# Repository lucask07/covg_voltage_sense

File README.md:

# COVG Voltage Sense Board

This board is physically small so it can be housed in an enclosure on a micromanipulator. The board input is a BNC connector which is compatible with glass microelectrode holders. 

The input amplifier must have low capacitance to minimize the total filter from the capacitance and the microelectrode resistance. The first version has a fixed amplifier gain. 

The **Rev_b board** modifications were designed and implemented by undergraduate student Jordan Haag. The board incorporates programmable gain and uses a low-noise voltage reference, REF3440, as the reference input to the offset adjust DAC. The low-noise reference improves the noise performance of the system. 

## Schematic
The [schematic](docs/voltage_sense.pdf) is in the DOCS folder.

## Fabrication
The second revision of this board was fabricated and assembled by JLCPCB. 

Order #: Y13-3276043A 

Assembly: SMT02402281623205-3276043A

Date: 2024/02/29

## Bill of Materials

The BOM is here  

Certain parts are not directly available from LCSC and so were pre-ordered. Pre-order: 24AA025UID, OPA1641,
DAC101C081CIMK/NOPB, TMUX6111PWR, TCA9555DBR, LP2981A-33DBVT, ADA4000-2ARZ-R7. Global sourcing: 3269W-1-103GLF, REF3440TIDBVR.

## Bugs and Future Improvement

* A footprint for a capacitor should be included in parallel with the feedback gain resistors, for example R33, R34, R35, and R36. This limits the amplifier bandwidth. Currently we work around this omission by stacking a capacitor on top of the resistor. Issue ([#4][i4])

[i4]: https://github.com/lucask07/covg_voltage_sense/issues/4

* U8,U10 (TMUX6111) and U11 (REF3440) were not assembled by JLCPCB and were lated added by hand.

## Upgrades 

This version addresses the following issues that occured with V1 

* DAC reference noise: https://github.com/lucask07/covg_voltage_sense/issues/5
* Negative capacitance connection: https://github.com/lucask07/covg_voltage_sense/issues/3
* C8 causes oscillation: https://github.com/lucask07/covg_voltage_sense/issues/2
* Incorrect BOM resistor values: https://github.com/lucask07/covg_voltage_sense/issues/1

## Miscellaneous

### HDMI: connection from DAQ to daughtercard 

The digital COVG project uses the concept of one main data acquisition board connected to an FPGA. The main data acquisition board has multiple channels that extend to daughtercards. The connection to each daughtercard allows for low-latency control by connections to high-speed ADCs and DACs on the daq board. For COVG the daughtercards are the bath clamp; the guard clamp; the voltage clamp and I force; and the V1/V2. The connectivity to the daughtercard is generalized and will be the same for each. 

An HDMI-A cable is used for input and output signals that connect the bath clamp daughtercard to the DAQ board. The HDMI cable carries:

- **power**: +5V, +15V, -15V
- **GND** 
- **Analog outputs** (to ADCs): 
	- OUT\_P, OUT\_N differential pair (x1) to 5 MSPS ADC 
	- single-ended out AMP\_OUT, CAL\_ADC both to individual channel of 1 MSPS ADC (ADS8686) 
- **Analog reference**: VCM: buffered ADC common-mode voltage (nominal 2.5 V)
- **Digital inputs** (from DACs): 
	- CMD: (command signal) from 1 us settling time DAC (attenuated by x10 at board)
	- CC: (capacitive compensation) from 1 us settling time DAC. AC coupled. 
	- CAL_DAC: from 5 us settling time DAC (DAC8050). Either voltage source or current source (Howland current pump), programmable on DAQ board
- **Digital control** (I2C): SDA, SCL (@ 3.3 V levels). Pull-ups are on DAQ board not on the daughtercards! The daughtercards use a TCA9555 I/O expander to generate many control signals from the I2C interface. 
- **Utiility** grab-bag connected to test-point. Jumper on DAQ board to set to analog in, analog out or digital I/O.

| Pin | HDMI name    | Generic Daughtercard     | Bath clamp | Notes  |
|-----|--------------|--------------|------------|---------------------------------------------------------------------------|
| 1   | Data2+       | fastDAC1     | CMD        | ~1 us settling time                      |
| 2   | Data2 shield | Gnd          | Gnd        |                                                                           |
| 3   | Data2-       | Analog/GPIO1 | CAL_DAC    | Analog input signal from DAC8050, 16 bit, 5us settle, 5 V supply                                                                         |
| 4   | Data1+       | fastADC+     | IM_P       | to AD7960/AD7961. Differential low-pass filter on DAQ board                                                                          |
| 5   | Data1 shield | Gnd          | Gnd        |                                                                           |
| 6   | Data1-       | fastADC-     | IM_N       | to AD7960/AD7961. Differential low-pass filter on DAQ board                                                                          |
| 7   | Data0+       | fastDAC2     | CC         | ~1 us settling time                                                                          |
| 8   | Data0 shield | Gnd          | Gnd        |                                                                           |
| 9   | Data0-       | Analog/GPIO2 | CAL_ADC    | to ADS8686 1 MSPS, programmable PGA for range up to +/-10V                                                           |
| 10  | Clock+       | 15V          | 15V        | From a linear regulator on the DAQ board, 75 mA max per channel                                                                         |
| 11  | Clock shield | Gnd          | Gnd        |                                                                           |
| 12  | Clock-       | VCM          | VCM        | buffered on DAQ board, nominal 2.5 V                                                                          |
| 13  | CEC          | -15V         | -15V       | From a linear regulator on the DAQ board, 75 mA max per channel                             |
| 14  | Reserved     | open         | open       | Resistor jumper on DAQ board sets as analog in, analog out, or digital I/O (@ 3.3 V levels). Default stuffing option is to connect to the general purpose ADC (ADS8686). |
| 15  | SCL          | SCL          | SCL        | I2C clock. Pull-up on main DAQ board, 3.3 V levels                |
| 16  | SDA          | SDA          | SDA        | I2C data. Pull-up on main DAQ board, 3.3 V levels                 |
| 17  | Gnd          | Gnd          | Gnd        |                                                                           |
| 18  | 5V           | 5V           | 5V         | Power input from linear regulator, 200 mA max per channel (target)  |
| 19  | HPD          | Analog/GPIO3 | AMP_OUT    | output to ADS8686 1 MSPS, programmable PGA                        |

### Acknowledgments

Research reported in this repository was supported by the National Institute Of Neurological Disorders And Stroke of the National Institutes of Health under Award Number R15NS116907. The content is solely the responsibility of the authors and does not necessarily represent the official views of the National Institutes of Health.

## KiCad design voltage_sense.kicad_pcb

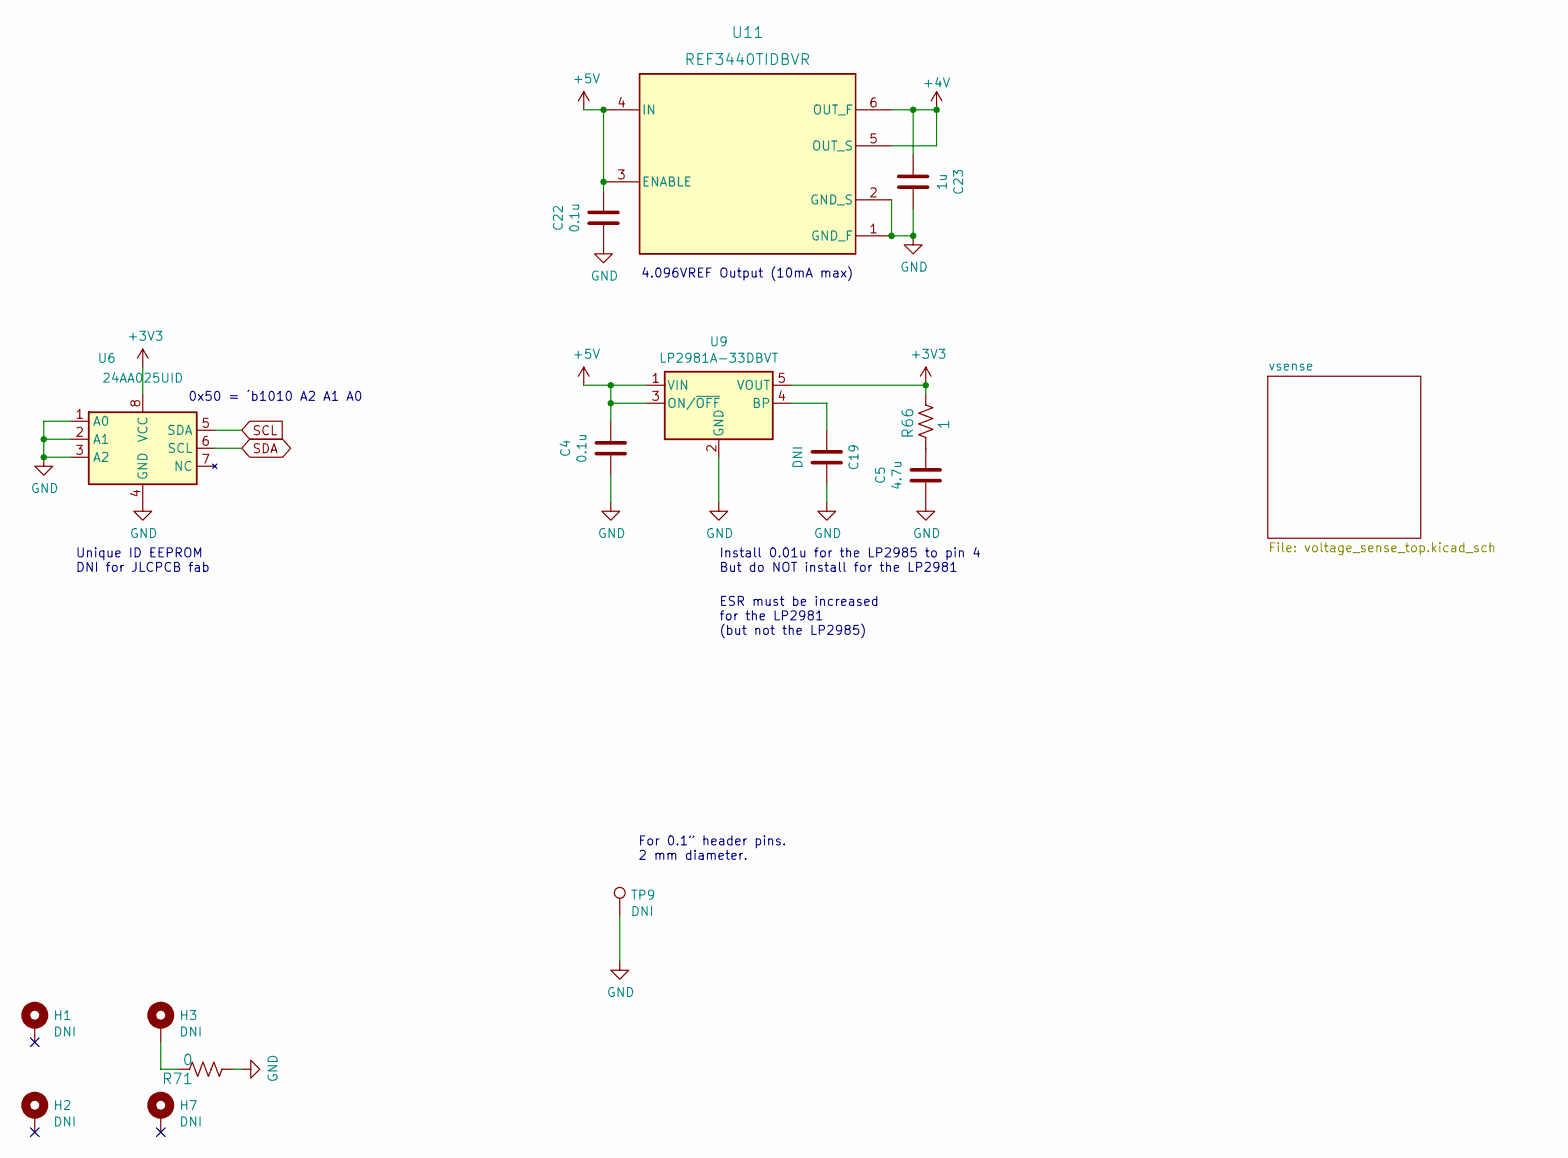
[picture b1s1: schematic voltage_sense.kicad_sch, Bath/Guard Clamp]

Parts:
C4, C22: 0.1u; C_0603_1608Metric; Tolerance 10%; voltage 25V
C5: 4.7u; C_0603_1608Metric; Tolerance 20%; voltage 25V
C19: DNI; C_0603_1608Metric
C23: 1u; C_0603_1608Metric; Tolerance 20%; voltage 25V
H1, H2, H7: DNI; MountingHole_2.2mm_M2
H3: DNI; MountingHole_2.2mm_M2_Pad
R66: 1; R_0603_1608Metric; Tolerance 1%
R71: 0; R_0603_1608Metric; Tolerance 1%
TP9: DNI; TestPoint_THTPad_D2.0mm_Drill1.0mm
U6: 24AA025UID; SOIC-8_3.9x4.9mm_P1.27mm
U9: LP2981A-33DBVT; SOT-23-5
U11: REF3440TIDBVR; REF3440

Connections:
+3V3: R66.1, U6.8 (VCC), U9.5 (VOUT); also elsewhere on the board
+4V: C23.2, U11.5 (OUT_S), U11.6 (OUT_F); also elsewhere on the board
+5V: C4.1, C22.1, U9.1 (VIN), U9.3 (ON/~OFF), U11.3 (ENABLE), U11.4 (IN); also elsewhere on the board
GND: C4.2, C5.2, C19.2, C22.2, C23.1, R71.2, TP9.1, U6.1 (A0), U6.2 (A1), U6.3 (A2), U6.4 (GND), U9.2 (GND), U11.1 (GND_F), U11.2 (GND_S); also elsewhere on the board
unnamed: C5.1, R66.2
unnamed: C19.1, U9.4 (BP)
unnamed: H3.1, R71.1
SCL: U6.5 (SDA); also elsewhere on the board
SDA: U6.6 (SCL); also elsewhere on the board

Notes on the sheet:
For 0.1” header pins. 2 mm diameter.
Install 0.01u for the LP2985 to pin 4 But do NOT install for the LP2981
Unique ID EEPROM DNI for JLCPCB fab
0x50 = ‘b1010 A2 A1 A0
4.096VREF Output (10mA max)
ESR must be increased for the LP2981 (but not the LP2985)

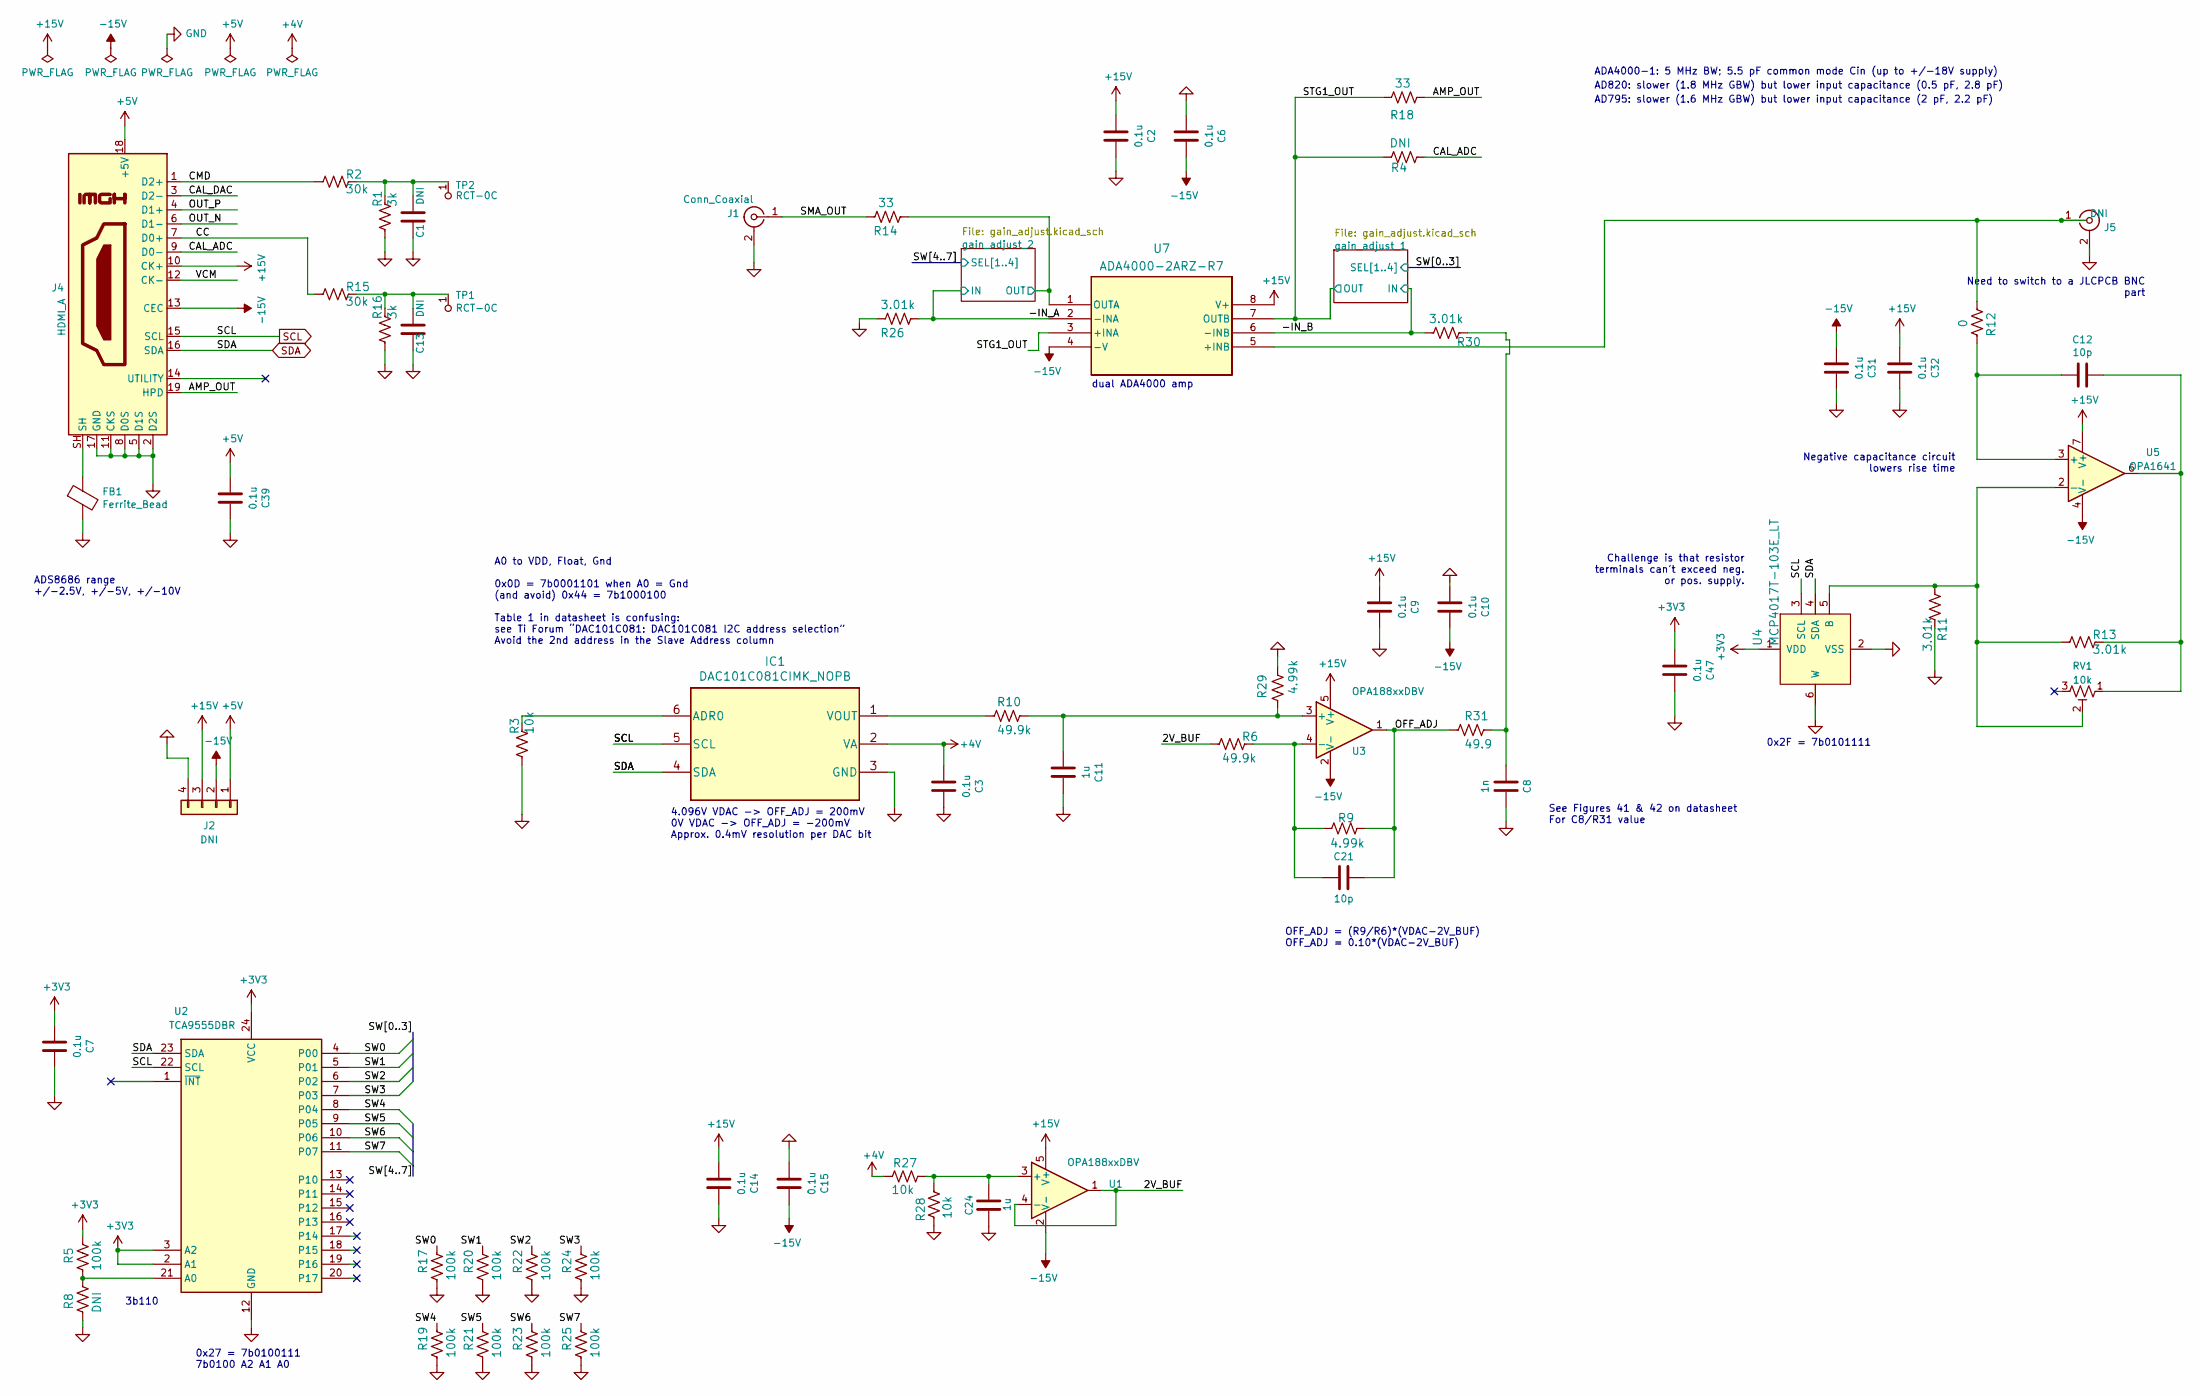
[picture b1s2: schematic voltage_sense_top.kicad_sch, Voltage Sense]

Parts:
C1, C13: DNI; C_0603_1608Metric; Tolerance 5%; voltage 50V
C2, C3, C6, C9, C10, C14, C15, C31, C39: 0.1u; C_0603_1608Metric; Tolerance 20%; voltage 25V
C7, C32, C47: 0.1u; C_0603_1608Metric; voltage 25V
C8: 1n; C_0603_1608Metric; Tolerance 20%; voltage 25V
C11, C24: 1u; C_0603_1608Metric; Tolerance 20%; voltage 25V
C12: 10p; C_0603_1608Metric; Tolerance 5%
C21: 10p; C_0603_1608Metric; Tolerance 20%; voltage 25V
FB1: Ferrite_Bead; C_1206_3216Metric
IC1: DAC101C081CIMK_NOPB; TSOT-23-6
J1: Conn_Coaxial; BU-SMA-G
J2: DNI; PinHeader_1x04_P2.54mm_Horizontal
J4: HDMI_A; CONN_10029449-111RLF_HDMI_A
J5: DNI; BNC_Amphenol_B6252HB-NPP3G-50_Horizontal
R1, R16: 3k; R_0603_1608Metric; Tolerance 1%
R2, R15: 30k; R_0603_1608Metric; Tolerance 1%
R3: 10k; R_0603_1608Metric; Tolerance 5%
R4, R8: DNI; R_0603_1608Metric; Tolerance 1%
R5, R17, R19, R20, R21, R22, R23, R24, R25: 100k; R_0603_1608Metric; Tolerance 1%
R6, R10: 49.9k; R_0603_1608Metric; Tolerance 1%
R9, R29: 4.99k; R_0603_1608Metric; Tolerance 1%
R11, R13, R26, R30: 3.01k; R_0603_1608Metric; Tolerance 1%
R12: 0; R_0603_1608Metric; Tolerance 1%
R14, R18: 33; R_0603_1608Metric; Tolerance 1%
R27, R28: 10k; R_0603_1608Metric; Tolerance 1%
R31: 49.9; R_0603_1608Metric; Tolerance 1%
RV1: 10k; TRIM_3269W-1-103GLF
TP1, TP2: RCT-0C; Test_Point_D1.02mm
U1, U3: OPA188xxDBV; TSOT-23-5
U2: TCA9555DBR; SSOP-24_5.3x8.2mm_P0.65mm
U4: MCP4017T-103E_LT; SOT-363; MPN MCP4017T-103E/LT; Digi-Key_PN MCP4017T-103E/LTCT-ND
U5: OPA1641; SOIC-8_3.9x4.9mm_P1.27mm
U7: ADA4000-2ARZ-R7; R_8_ADI

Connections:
+3V3: C7.2, C47.2, R5.1, U2.2 (A1), U2.3 (A2), U2.24 (VCC), U4.1 (VDD); also elsewhere on the board
+4V: C3.2, IC1.2 (VA), R27.2; also elsewhere on the board
+5V: C39.2, J2.1, J4.18 (+5V); also elsewhere on the board
+15V: C2.2, C9.2, C14.2, C32.2, J2.3, J4.10 (CK+), U1.5 (V+), U3.5 (V+), U5.7 (V+), U7.8 (V+); also elsewhere on the board
-15V: C6.1, C10.1, C15.1, C31.2, J2.2, J4.13 (CEC), U1.2 (V-), U3.2 (V-), U5.4 (V-), U7.4 (-V); also elsewhere on the board
/vsense/2V_BUF: R6.2, U1.1, U1.4 (-)
/vsense/-IN_A: R26.2, U7.2 (-INA); also elsewhere on the board
/vsense/-IN_B: R30.1, U7.6 (-INB); also elsewhere on the board
/vsense/AMP_OUT: J4.19 (HPD), R18.2
/vsense/CAL_ADC: J4.9 (D0-), R4.2
/vsense/CAL_DAC: J4.3 (D2-)
/vsense/CC: J4.7 (D0+), R15.2
/vsense/CMD: J4.1 (D2+), R2.2
/vsense/OFF_ADJ: C21.1, R9.1, R31.2, U3.1
/vsense/OUT_N: J4.6 (D1-)
/vsense/OUT_P: J4.4 (D1+)
/vsense/SMA_OUT: J1.1 (In), R14.1
/vsense/STG1_OUT: R4.1, R18.1, U7.3 (+INA), U7.7 (OUTB); also elsewhere on the board
/vsense/SW0: R17.1, U2.4 (P00); also elsewhere on the board
/vsense/SW1: R20.1, U2.5 (P01); also elsewhere on the board
/vsense/SW2: R22.1, U2.6 (P02); also elsewhere on the board
/vsense/SW3: R24.1, U2.7 (P03); also elsewhere on the board
/vsense/SW4: R19.1, U2.8 (P04); also elsewhere on the board
/vsense/SW5: R21.1, U2.9 (P05); also elsewhere on the board
/vsense/SW6: R23.1, U2.10 (P06); also elsewhere on the board
/vsense/SW7: R25.1, U2.11 (P07); also elsewhere on the board
/vsense/VCM: J4.12 (CK-)
/vsense/gain_adjust_2/OUT: R14.2, U7.1 (OUTA); also elsewhere on the board
GND: C1.1, C2.1, C3.1, C6.2, C7.1, C8.1, C9.1, C10.2, C11.1, C13.1, C14.1, C15.2, C24.1, C31.1, C32.1, C39.1, C47.1, FB1.2, IC1.3 (GND), J1.2 (Ext), J2.4, J4.2 (D2S), J4.5 (D1S), J4.8 (D0S), J4.11 (CKS), J4.17 (GND), J5.2 (Ext), R1.2, R3.2, R8.2, R11.1, R16.2, R17.2, R19.2, R20.2, R21.2, R22.2, R23.2, R24.2, R25.2, R26.1, R28.2, R29.1, U2.12 (GND), U4.2 (VSS), U4.6 (W); also elsewhere on the board
unnamed: C1.2, R1.1, R2.1, TP2.1
unnamed: C8.2, R30.2, R31.1
unnamed: C11.2, R10.1, R29.2, U3.3 (+)
unnamed: C12.1, R13.1, RV1.1, U5.6
unnamed: C12.2, R12.1, U5.3 (+)
unnamed: C13.2, R15.1, R16.1, TP1.1
unnamed: C21.2, R6.1, R9.2, U3.4 (-)
unnamed: C24.2, R27.1, R28.1, U1.3 (+)
unnamed: FB1.1, J4.SH
unnamed: IC1.1 (VOUT), R10.2
unnamed: IC1.6 (ADR0), R3.1
unnamed: J5.1 (In), R12.2, U7.5 (+INB)
unnamed: R5.2, R8.1, U2.21 (A0)
unnamed: R11.2, R13.2, RV1.2, U4.5 (B), U5.2 (-)
SCL: IC1.5 (SCL), J4.15 (SCL), U2.22 (SCL), U4.3 (SCL); also elsewhere on the board
SDA: IC1.4 (SDA), J4.16 (SDA), U2.23 (SDA), U4.4 (SDA); also elsewhere on the board

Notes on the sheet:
0x27 = 7b0100111 7b0100 A2 A1 A0
AD795: slower (1.6 MHz GBW) but lower input capacitance (2 pF, 2.2 pF)
Negative capacitance circuit lowers rise time
Challenge is that resistor terminals can't exceed neg. or pos. supply.
4.096V VDAC -> OFF_ADJ = 200mV 0V VDAC -> OFF_ADJ = -200mV Approx. 0.4mV resolution per DAC bit
dual ADA4000 amp
0x2F = 7b0101111
OFF_ADJ = (R9/R6)*(VDAC-2V_BUF) OFF_ADJ = 0.10*(VDAC-2V_BUF)
ADS8686 range +/-2.5V, +/-5V, +/-10V
AD820: slower (1.8 MHz GBW) but lower input capacitance (0.5 pF, 2.8 pF)
See Figures 41 & 42 on datasheet For C8/R31 value
A0 to VDD, Float, Gnd 0x0D = 7b0001101 when A0 = Gnd (and avoid) 0x44 = 7b1000100 Table 1 in datasheet is confusing: see Ti Forum “DAC101C081: DAC101C081 I2C address selection” Avoid the 2nd address in the Slave Address column
3b110
Need to switch to a JLCPCB BNC part
ADA4000-1: 5 MHz BW; 5.5 pF common mode Cin (up to +/-18V supply)

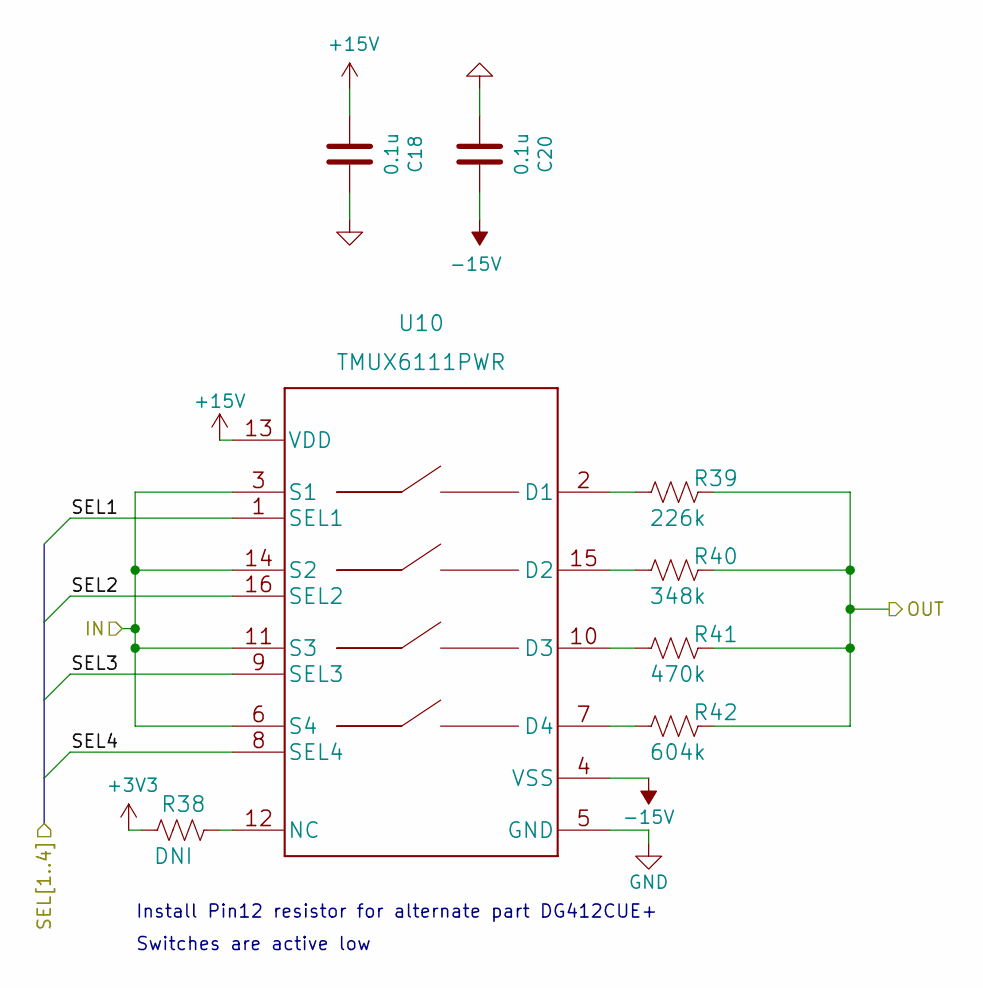
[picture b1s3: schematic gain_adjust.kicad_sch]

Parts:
C18, C20: 0.1u; C_0603_1608Metric; Tolerance 20%; voltage 25V
R38: DNI; R_0603_1608Metric; Tolerance 1%
R39: 226k; R_0603_1608Metric; Tolerance 1%
R40: 348k; R_0603_1608Metric; Tolerance 1%
R41: 470k; R_0603_1608Metric; Tolerance 1%
R42: 604k; R_0603_1608Metric; Tolerance 1%
U10: TMUX6111PWR; PW0016A_N

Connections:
+3V3: R38.1; also elsewhere on the board
+15V: C18.2, U10.13 (VDD); also elsewhere on the board
-15V: C20.1, U10.4 (VSS); also elsewhere on the board
/vsense/-IN_A: U10.3 (S1), U10.6 (S4), U10.11 (S3), U10.14 (S2); also elsewhere on the board
/vsense/SW4: U10.1 (SEL1); also elsewhere on the board
/vsense/SW5: U10.16 (SEL2); also elsewhere on the board
/vsense/SW6: U10.9 (SEL3); also elsewhere on the board
/vsense/SW7: U10.8 (SEL4); also elsewhere on the board
/vsense/gain_adjust_2/OUT: R39.1, R40.1, R41.1, R42.1; also elsewhere on the board
GND: C18.1, C20.2, U10.5 (GND); also elsewhere on the board
unnamed: R38.2, U10.12 (NC)
unnamed: R39.2, U10.2 (D1)
unnamed: R40.2, U10.15 (D2)
unnamed: R41.2, U10.10 (D3)
unnamed: R42.2, U10.7 (D4)

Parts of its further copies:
C16, C17: 0.1u; C_0603_1608Metric; Tolerance 20%; voltage 25V
R32: DNI; R_0603_1608Metric; Tolerance 1%
R33: 226k; R_0603_1608Metric; Tolerance 1%
R34: 348k; R_0603_1608Metric; Tolerance 1%
R35: 470k; R_0603_1608Metric; Tolerance 1%
R36: 604k; R_0603_1608Metric; Tolerance 1%
U8: TMUX6111PWR; PW0016A_N

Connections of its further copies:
+3V3: R32.1; also elsewhere on the board
+15V: C16.2, U8.13 (VDD); also elsewhere on the board
-15V: C17.1, U8.4 (VSS); also elsewhere on the board
/vsense/-IN_B: U8.3 (S1), U8.6 (S4), U8.11 (S3), U8.14 (S2); also elsewhere on the board
/vsense/STG1_OUT: R33.1, R34.1, R35.1, R36.1; also elsewhere on the board
/vsense/SW0: U8.1 (SEL1); also elsewhere on the board
/vsense/SW1: U8.16 (SEL2); also elsewhere on the board
/vsense/SW2: U8.9 (SEL3); also elsewhere on the board
/vsense/SW3: U8.8 (SEL4); also elsewhere on the board
GND: C16.1, C17.2, U8.5 (GND); also elsewhere on the board
unnamed: R32.2, U8.12 (NC)
unnamed: R33.2, U8.2 (D1)
unnamed: R34.2, U8.15 (D2)
unnamed: R35.2, U8.10 (D3)
unnamed: R36.2, U8.7 (D4)

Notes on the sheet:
Install Pin12 resistor for alternate part DG412CUE+
Switches are active low

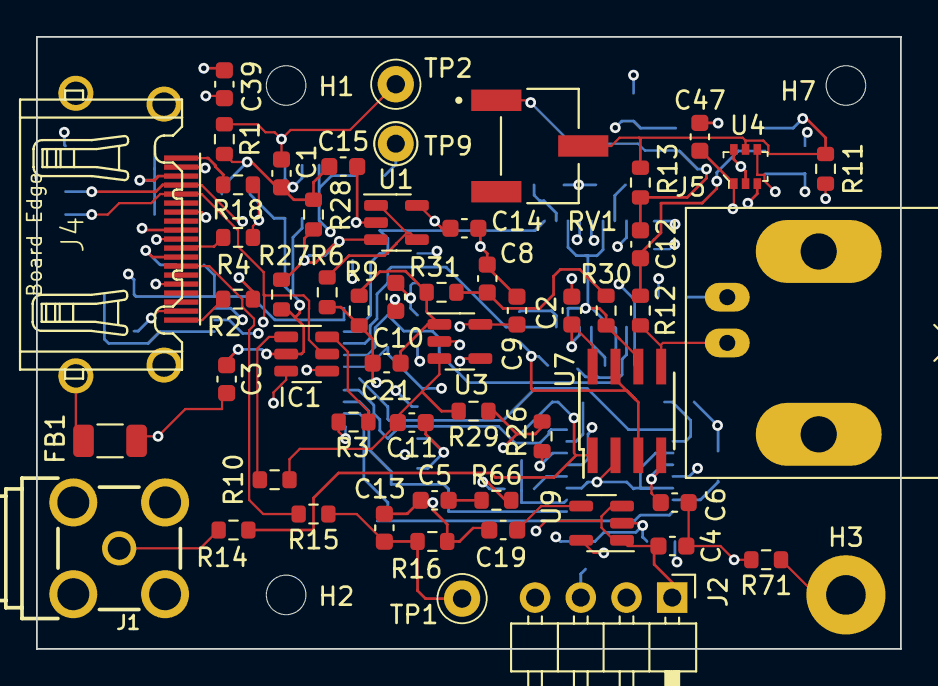
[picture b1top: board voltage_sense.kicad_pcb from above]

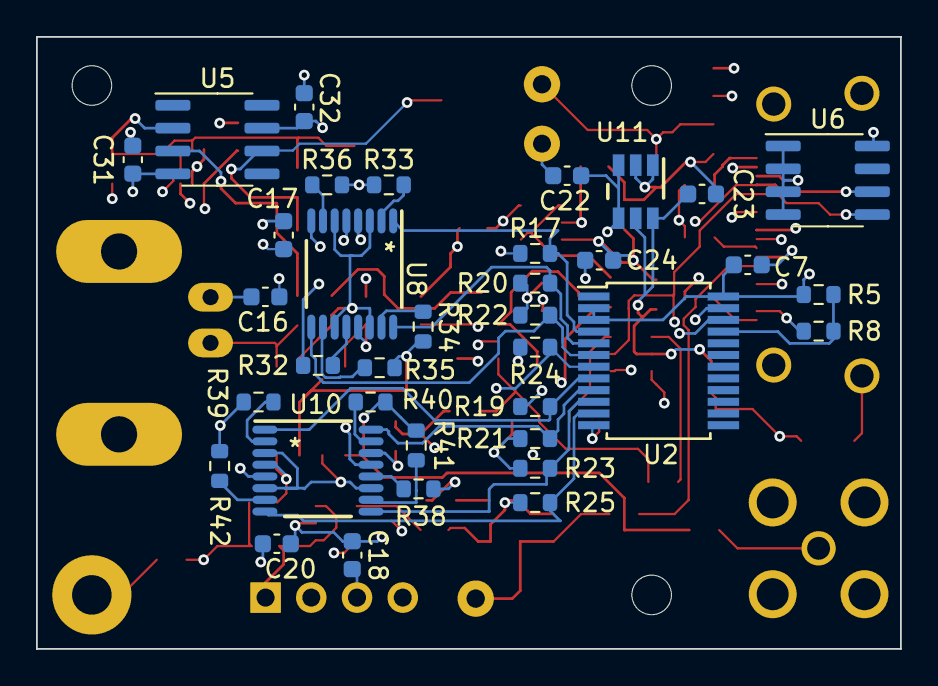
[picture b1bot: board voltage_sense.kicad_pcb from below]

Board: 6 copper layers, 48.0 x 34.0 mm, 95 parts (36 on the bottom side), 54 nets.

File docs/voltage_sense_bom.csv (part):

"Source:","C:\Users\twinj\COVG\KiCAD\Working\covg_voltage_sense\voltage_sense.kicad_sch"
"Date:","1/23/2024 2:28:45 PM"
"Tool:","Eeschema (6.0.11)"
"Generator:","C:\Program Files\KiCad\6.0\bin\scripting\plugins/bom_csv_grouped_by_value.py"
"Component Count:","95"

"Individual Components:"

"Item","Qty","Reference(s)","Value","LibPart","Footprint","Datasheet","Alternate Manf#","Alternate2 Manf#","Alternate3 Manf#","Category","DK_Datasheet_Link","DK_Detail_Page","Description","Digi-Key_PN","Family","MPN","Manf#","Manufacturer","Status","Tolerance","voltage"
"","","C1","DNI","Device:C","Capacitor_SMD:C_0603_1608Metric","~","","","","","","","","","","","CC0603JRNPO9BN100","","","5%","50V"
"","","C2","0.1u","Device:C","Capacitor_SMD:C_0603_1608Metric","~","","","","","","","","","","","CC0603MRX7R8BB104","","","20%","25V"
"","","C3","0.1u","Device:C","Capacitor_SMD:C_0603_1608Metric","~","","","","","","","","","","","CC0603MRX7R8BB104","","","20%","25V"
"","","C4","0.1u","Device:C","Capacitor_SMD:C_0603_1608Metric","~","","","","","","","","","","","CL10B104KA8NNWC","","","10%","25V"
"","","C5","4.7u","Device:C","Capacitor_SMD:C_0603_1608Metric","~","","","","","","","","","","","CL10A475KP8NNNC","","","20%","25V"
"","","C6","0.1u","Device:C","Capacitor_SMD:C_0603_1608Metric","~","","","","","","","","","","","CC0603MRX7R8BB104","","","20%","25V"
"","","C7","0.1u","Device:C","Capacitor_SMD:C_0603_1608Metric","~","","","","","","","","","","","CC0603MRX7R8BB104","","","","25V"
"","","C8","1n","Device:C","Capacitor_SMD:C_0603_1608Metric","~","","","","","","","","","","","CC0603KRX7R8BB102","","","20%","25V"
"","","C9","0.1u","Device:C","Capacitor_SMD:C_0603_1608Metric","~","","","","","","","","","","","CC0603MRX7R8BB104","","","20%","25V"
"","","C10","0.1u","Device:C","Capacitor_SMD:C_0603_1608Metric","~","","","","","","","","","","","CC0603MRX7R8BB104","","","20%","25V"
"","","C11","1u","Device:C","Capacitor_SMD:C_0603_1608Metric","~","","","","","","","","","","","CC0603KRX7R7BB105","","","20%","25V"
"","","C12","10p","Device:C","Capacitor_SMD:C_0603_1608Metric","~","","","","","","","","","","","CC0603JRNPO8BN100","","","5%",""
"","","C13","DNI","Device:C","Capacitor_SMD:C_0603_1608Metric","~","","","","","","","","","","","CC0603JRNPO9BN100","","","5%","50V"
"","","C14","0.1u","Device:C","Capacitor_SMD:C_0603_1608Metric","~","","","","","","","","","","","CC0603MRX7R8BB104","","","20%","25V"
"","","C15","0.1u","Device:C","Capacitor_SMD:C_0603_1608Metric","~","","","","","","","","","","","CC0603MRX7R8BB104","","","20%","25V"
"","","C16","0.1u","Device:C","Capacitor_SMD:C_0603_1608Metric","~","","","","","","","","","","","CC0603MRX7R8BB104","","","20%","25V"
"","","C17","0.1u","Device:C","Capacitor_SMD:C_0603_1608Metric","~","","","","","","","","","","","CC0603MRX7R8BB104","","","20%","25V"
"","","C18","0.1u","Device:C","Capacitor_SMD:C_0603_1608Metric","~","","","","","","","","","","","CC0603MRX7R8BB104","","","20%","25V"
"","","C19","DNI","Device:C","Capacitor_SMD:C_0603_1608Metric","~","","","","","","","","","","","","","","",""
"","","C20","0.1u","Device:C","Capacitor_SMD:C_0603_1608Metric","~","","","","","","","","","","","CC0603MRX7R8BB104","","","20%","25V"
"","","C21","10p","Device:C","Capacitor_SMD:C_0603_1608Metric","~","","","","","","","","","","","CC0603JRNPO9BN100","","","20%","25V"
"","","C22","0.1u","Device:C","Capacitor_SMD:C_0603_1608Metric","~","","","","","","","","","","","CL10B104KA8NNWC","","","10%","25V"
"","","C23","1u","Device:C","Capacitor_SMD:C_0603_1608Metric","~","","","","","","","","","","","CC0603KRX7R7BB105","","","20%","25V"
"","","C24","1u","Device:C","Capacitor_SMD:C_0603_1608Metric","~","","","","","","","","","","","CC0603KRX7R7BB105","","","20%","25V"
"","","C31","0.1u","Device:C","Capacitor_SMD:C_0603_1608Metric","~","","","","","","","","","","","CC0603MRX7R8BB104","","","20%","25V"
"","","C32","0.1u","Device:C","Capacitor_SMD:C_0603_1608Metric","~","","","","","","","","","","","CC0603MRX7R8BB104","","","","25V"
"","","C39","0.1u","Device:C","Capacitor_SMD:C_0603_1608Metric","~","","","","","","","","","","","CC0603MRX7R8BB104","","","20%","25V"
"","","C47","0.1u","Device:C","Capacitor_SMD:C_0603_1608Metric","~","","","","","","","","","","","CC0603MRX7R8BB104","","","","25V"
"","","FB1","Ferrite_Bead","bath_clamp-rescue:Ferrite_Bead-Device","Capacitor_SMD:C_1206_3216Metric","","","","","","","","","","","","BLM31PG500SN1L","","","",""
"","","H1","DNI","Mechanical:MountingHole_Pad","MountingHole:MountingHole_2.2mm_M2","~","","","","","","","","","","","","","","",""
"","","H2","DNI","Mechanical:MountingHole_Pad","MountingHole:MountingHole_2.2mm_M2","~","","","","","","","","","","","","","","",""
"","","H3","DNI","Mechanical:MountingHole_Pad","MountingHole:MountingHole_2.2mm_M2_Pad","~","","","","","","","","","","","","","","",""
"","","H7","DNI","Mechanical:MountingHole_Pad","MountingHole:MountingHole_2.2mm_M2","~","","","","","","","","","","","","","","",""
"","","IC1","DAC101C081CIMK_NOPB","covg-kicad:DAC101C081CIMK_NOPB","Package_TO_SOT_SMD:TSOT-23-6","","DAC121C081CIMK/NOPB","","","","","","","","","","DAC101C081CIMK/NOPB","","","",""
"","","J1","Conn_Coaxial","Connector:Conn_Coaxial","covg-kicad:BU-SMA-G"," ~","","","","","","","","","","","C2874827","","","",""
"","","J2","DNI","Connector_Generic:Conn_01x04","Connector_PinHeader_2.54mm:PinHeader_1x04_P2.54mm_Horizontal","~","","","","","","","","","","","","","","",""
"","","J4","HDMI_A","Connector:HDMI_A","covg-kicad:CONN_10029449-111RLF_HDMI_A","https://en.wikipedia.org/wiki/HDMI","","","","","","","","","","","10029449-111RLF","","","",""
"","","J5","Conn_Coaxial","Connector:Conn_Coaxial","Connector_Coaxial:BNC_Amphenol_B6252HB-NPP3G-50_Horizontal"," ~","","","","","","","","","","","C2874827","","","",""
"","","R1","3k","Device:R_US","Resistor_SMD:R_0603_1608Metric","~","","","","","","","","","","","RC0603FR-073KL","","","1%",""
"","","R2","30k","Device:R_US","Resistor_SMD:R_0603_1608Metric","~","","","","","","","","","","","RC0603FR-0730KL","","","1%",""
"","","R3","10k","Device:R_US","Resistor_SMD:R_0603_1608Metric","~","","","","","","","","","","","RC0603FR-0710KL","","","5%",""
"","","R4","DNI","Device:R_US","Resistor_SMD:R_0603_1608Metric","~","","","","","","","","","","","","","","1%",""
"","","R5","100k","Device:R_US","Resistor_SMD:R_0603_1608Metric","~","","","","","","","","","","","RC0603FR-07100KL","","","1%",""
"","","R6","50k","Device:R_US","Resistor_SMD:R_0603_1608Metric","~","","","","","","","","","","","RT0603BRB0749K9L","","","1%",""
"","","R8","DNI","Device:R_US","Resistor_SMD:R_0603_1608Metric","~","","","","","","","","","","","RC0603FR-07100KL","","","1%",""
"","","R9","5k","Device:R_US","Resistor_SMD:R_0603_1608Metric","~","","","","","","","","","","","RT0603BRB074K99L","","","1%",""
"","","R10","50k","Device:R_US","Resistor_SMD:R_0603_1608Metric","~","","","","","","","","","","","RT0603BRB0749K9L","","","1%",""
"","","R11","3.01k","Device:R_US","Resistor_SMD:R_0603_1608Metric","~","","","","","","","","","","","RC0603JR-070RL","","","1%",""
"","","R12","0","Device:R_US","Resistor_SMD:R_0603_1608Metric","~","","","","","","","","","","","RC0603FR-073k01L","","","1%",""
"","","R13","3.01k","Device:R_US","Resistor_SMD:R_0603_1608Metric","~","","","","","","","","","","","RC0603FR-073k01L","","","1%",""
"","","R14","33","Device:R_US","Resistor_SMD:R_0603_1608Metric","~","","","","","","","","","","","RC0603FR-0733RL","","","1%",""
"","","R15","30k","Device:R_US","Resistor_SMD:R_0603_1608Metric","~","","","","","","","","","","","RC0603FR-0730KL","","","1%",""
"","","R16","3k","Device:R_US","Resistor_SMD:R_0603_1608Metric","~","","","","","","","","","","","RC0603FR-073KL","","","1%",""
"","","R17","100k","Device:R_US","Resistor_SMD:R_0603_1608Metric","~","","","","","","","","","","","RC0603FR-07100KL","","","1%",""
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
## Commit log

2023-05-17 found LCSC alternatives for some parts
2023-05-17 first draft of production files
2023-05-29 moved SMA to same size as HDMI
2023-05-29 files sent to JLCPCB; Order Y10-3276043A, SMT02305291257986-3276043A
2024-01-29 upload jlcpcb fab files and updated schematic/layout
2024-02-01 add gerbers
2024-02-01 add gerbers to jlcpcb
2024-02-12 update README file and add pdf schematics
2024-02-27 All production files in jlcpcb/production_files
2024-05-23 add gain calculations and bit encoding spreadsheet
2024-07-14 add modified production files; schematic update by KiCAD version to 8.0.1
2024-07-14 small edits to README.md
2024-07-14 add Gain calculations from main branch
2024-07-14 add schematic plot to the docs folder
2024-07-14 updates to README to include assembly info
2024-07-14 remove gain calculations and update README acknowledgments
2024-07-15 Update README.md with issue #4
